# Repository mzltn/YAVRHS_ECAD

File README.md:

# YAVRHS_ECAD

Yet another VR headset.

YAVRHS © 2024 by Zoltán Mánya is licensed under CC BY-NC-SA 4.0

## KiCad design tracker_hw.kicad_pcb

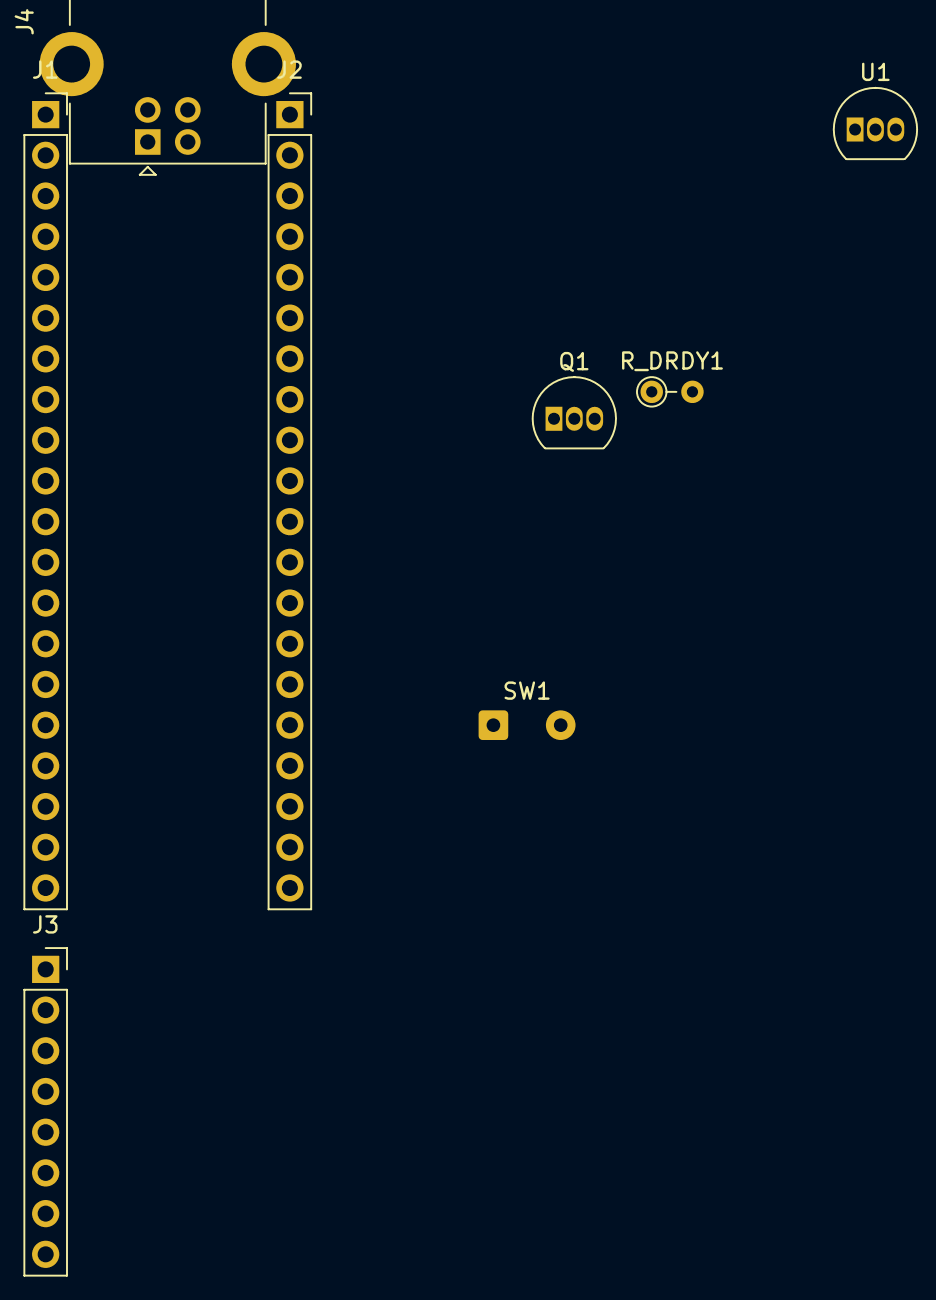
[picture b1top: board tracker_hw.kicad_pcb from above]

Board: 2 copper layers, 8 parts (0 on the bottom side), 12 nets, no tracks yet.

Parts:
J1, J2: Conn_01x20_Female; PinSocket_1x20_P2.54mm_Vertical
J3: Conn_01x08_Female; PinSocket_1x08_P2.54mm_Vertical
J4: USB_B; USB_B_Lumberg_2411_02_Horizontal
Q1: BS250; TO-92_Inline
R_DRDY1: 2.2K; R_Axial_DIN0204_L3.6mm_D1.6mm_P2.54mm_Vertical
SW1: SW_Push; SolderWire-0.25sqmm_1x02_P4.2mm_D0.65mm_OD1.7mm
U1: LP2950-3.3_TO92; TO-92_Inline

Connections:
A0: J2.15, Q1.2 (G)
A1: J2.14, SW1.1
A11: J1.8, J4.2 (D-)
A12: J1.9, J4.3 (D+)
B6: J1.14, J3.4
B7: J1.15, J3.5
B8: J1.16, R_DRDY1.1
DRDY: J3.8, R_DRDY1.2
GND: J1.19, J2.2, J3.3, J4.4 (GND), SW1.2, U1.2 (GND)
unnamed: Q1.1 (D), U1.3 (VI)
V5: J1.18, J2.1, J4.1 (VBUS), Q1.3 (S)
V_IMU: J3.2, U1.1 (VO)

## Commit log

2023-12-21 store
